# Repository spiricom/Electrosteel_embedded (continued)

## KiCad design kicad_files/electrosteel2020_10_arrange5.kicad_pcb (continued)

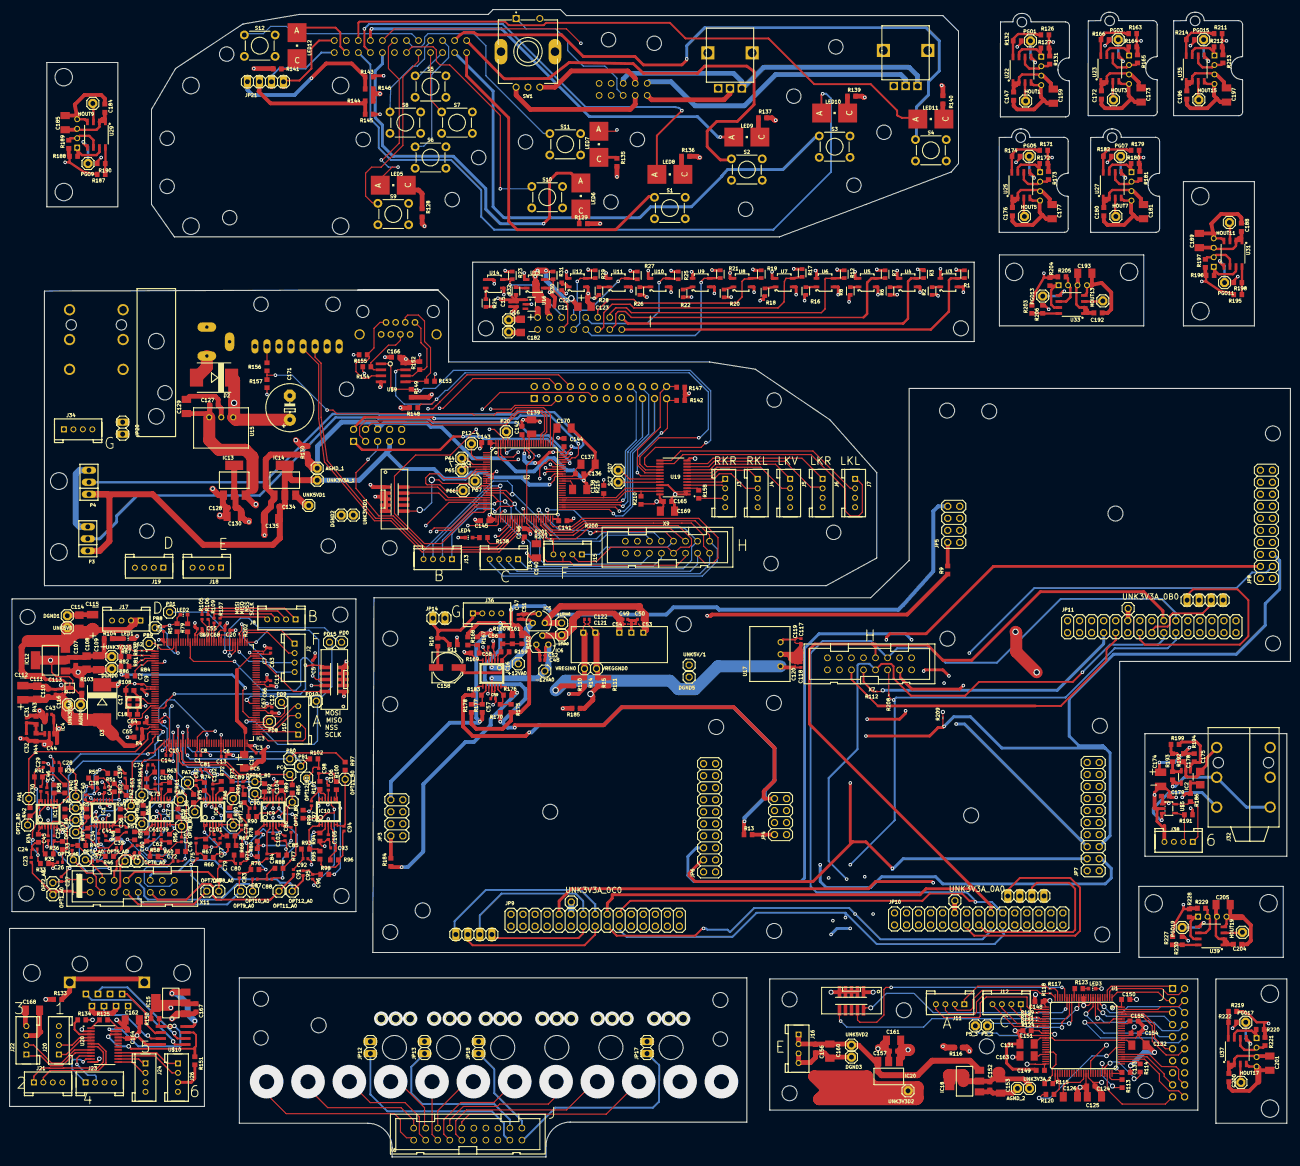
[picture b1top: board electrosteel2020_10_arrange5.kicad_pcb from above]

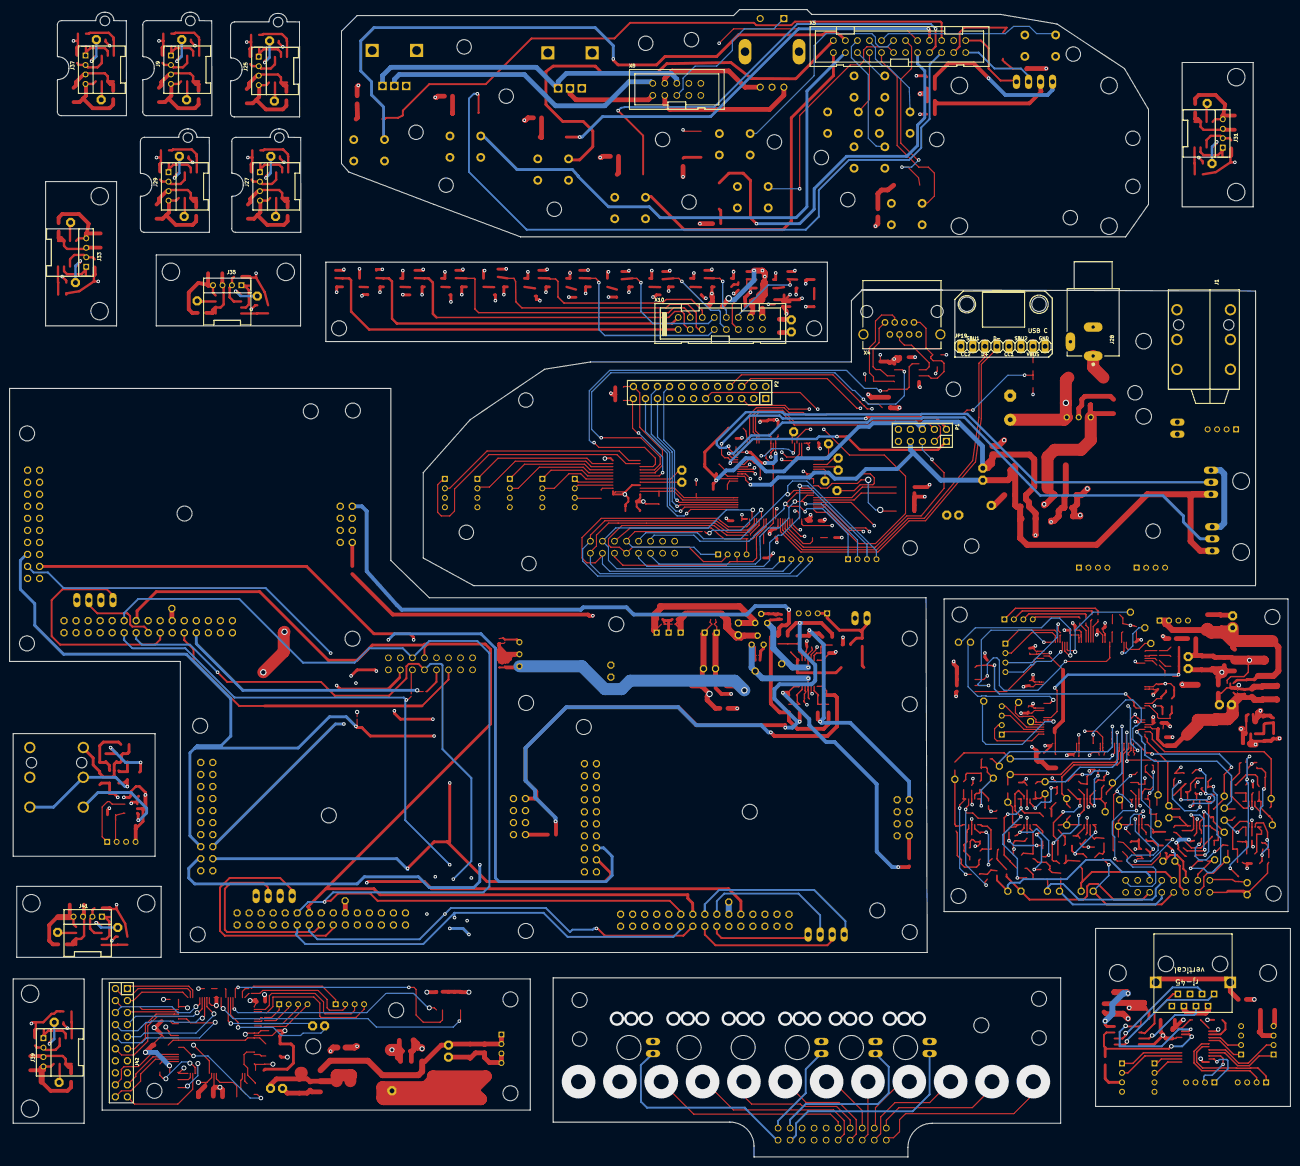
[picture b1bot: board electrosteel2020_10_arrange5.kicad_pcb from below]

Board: 4 copper layers, 270.5 x 242.3 mm, 770 parts (21 on the bottom side), 529 nets.

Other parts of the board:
R210, R215: 1.5k; R0603_16378527
SC7: 1X01
SD7: 1X01
UNK_HOLE_0: dummyfp0
UNK_HOLE_1: dummyfp1
UNK_HOLE_2: dummyfp2
UNK_HOLE_3: dummyfp3
UNK_HOLE_4: dummyfp4
UNK_HOLE_5: dummyfp5
UNK_HOLE_6: dummyfp6
UNK_HOLE_7: dummyfp7
UNK_HOLE_8: dummyfp8
UNK_HOLE_9: dummyfp9
UNK_HOLE_10: dummyfp10
UNK_HOLE_11: dummyfp11
UNK_HOLE_12: dummyfp12
UNK_HOLE_13: dummyfp13
UNK_HOLE_14: dummyfp14
UNK_HOLE_15: dummyfp15
UNK_HOLE_16: dummyfp16
UNK_HOLE_17: dummyfp17
UNK_HOLE_18: dummyfp18
UNK_HOLE_19: dummyfp19
UNK_HOLE_20: dummyfp20
UNK_HOLE_21: dummyfp21
UNK_HOLE_22: dummyfp22
UNK_HOLE_23: dummyfp23
UNK_HOLE_24: dummyfp24
UNK_HOLE_25: dummyfp25
UNK_HOLE_26: dummyfp26
UNK_HOLE_27: dummyfp27
UNK_HOLE_28: dummyfp28
UNK_HOLE_29: dummyfp29
UNK_HOLE_30: dummyfp30
UNK_HOLE_31: dummyfp31
UNK_HOLE_32: dummyfp32
UNK_HOLE_33: dummyfp33
UNK_HOLE_34: dummyfp34
UNK_HOLE_35: dummyfp35
UNK_HOLE_36: dummyfp36
UNK_HOLE_37: dummyfp37
UNK_HOLE_38: dummyfp38
UNK_HOLE_39: dummyfp39
UNK_HOLE_40: dummyfp40
UNK_HOLE_41: dummyfp41
UNK_HOLE_42: dummyfp42
UNK_HOLE_43: dummyfp43
UNK_HOLE_44: dummyfp44
UNK_HOLE_45: dummyfp45
UNK_HOLE_46: dummyfp46
UNK_HOLE_47: dummyfp47
UNK_HOLE_48: dummyfp48
UNK_HOLE_49: dummyfp49
UNK_HOLE_50: dummyfp50
UNK_HOLE_51: dummyfp51
UNK_HOLE_52: dummyfp52
UNK_HOLE_53: dummyfp53
UNK_HOLE_54: dummyfp54
UNK_HOLE_55: dummyfp55
UNK_HOLE_56: dummyfp56
UNK_HOLE_57: dummyfp57
UNK_HOLE_58: dummyfp58
UNK_HOLE_59: dummyfp59
UNK_HOLE_60: dummyfp60
UNK_HOLE_61: dummyfp61
UNK_HOLE_62: dummyfp62
UNK_HOLE_63: dummyfp63
UNK_HOLE_64: dummyfp64
UNK_HOLE_65: dummyfp65
UNK_HOLE_66: dummyfp66
UNK_HOLE_67: dummyfp67
UNK_HOLE_68: dummyfp68
UNK_HOLE_69: dummyfp69
UNK_HOLE_70: dummyfp70
UNK_HOLE_71: dummyfp71
UNK_HOLE_72: dummyfp72
UNK_HOLE_73: dummyfp73
UNK_HOLE_74: dummyfp74
UNK_HOLE_75: dummyfp75
UNK_HOLE_76: dummyfp76
UNK_HOLE_77: dummyfp77
UNK_HOLE_78: dummyfp78
UNK_HOLE_79: dummyfp79
UNK_HOLE_80: dummyfp80
UNK_HOLE_81: dummyfp81
UNK_HOLE_82: dummyfp82
UNK_HOLE_83: dummyfp83
UNK_HOLE_84: dummyfp84
UNK_HOLE_85: dummyfp85
UNK_HOLE_86: dummyfp86
UNK_HOLE_87: dummyfp87
UNK_HOLE_88: dummyfp88
UNK_HOLE_89: dummyfp89
UNK_HOLE_90: dummyfp90
UNK_HOLE_91: dummyfp91

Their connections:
3V3D5: R210.1, R215.2; also elsewhere on the board
unnamed 359: SD7.1; also elsewhere on the board
unnamed 360: SC7.1; also elsewhere on the board
SCL_B: R215.1; also elsewhere on the board
SDA_B: R210.2; also elsewhere on the board

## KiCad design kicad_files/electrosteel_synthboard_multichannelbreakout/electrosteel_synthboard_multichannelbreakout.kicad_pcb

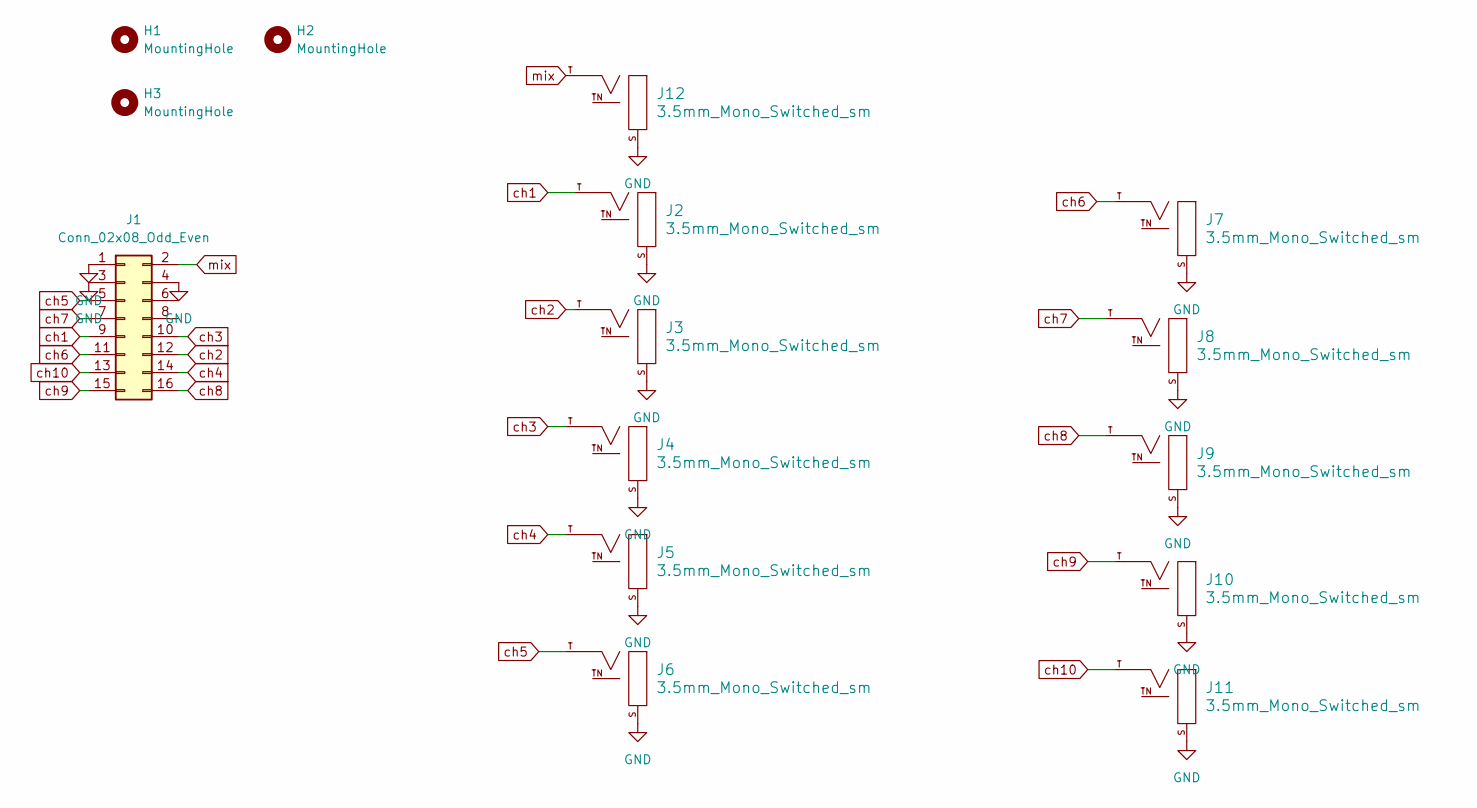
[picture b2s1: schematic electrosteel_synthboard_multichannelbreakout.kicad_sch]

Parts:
H1, H2, H3: MountingHole; MountingHole_3.2mm_M3
J1: Conn_02x08_Odd_Even; IDC-Header_2x08_P2.54mm_Vertical
J2, J3, J4, J5, J6, J7, J8, J9, J10, J11, J12: 3.5mm_Mono_Switched_sm; EighthInch_PJ398SM; Part Number WQP-WQP518MA

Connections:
GND: J1.1, J1.3, J1.4, J2.S (SHEILD), J3.S (SHEILD), J4.S (SHEILD), J5.S (SHEILD), J6.S (SHEILD), J7.S (SHEILD), J8.S (SHEILD), J9.S (SHEILD), J10.S (SHEILD), J11.S (SHEILD), J12.S (SHEILD)
ch1: J1.9, J2.T (SIG)
ch2: J1.12, J3.T (SIG)
ch3: J1.10, J4.T (SIG)
ch4: J1.14, J5.T (SIG)
ch5: J1.5, J6.T (SIG)
ch6: J1.11, J7.T (SIG)
ch7: J1.7, J8.T (SIG)
ch8: J1.16, J9.T (SIG)
ch9: J1.15, J10.T (SIG)
ch10: J1.13, J11.T (SIG)
mix: J1.2, J12.T (SIG)

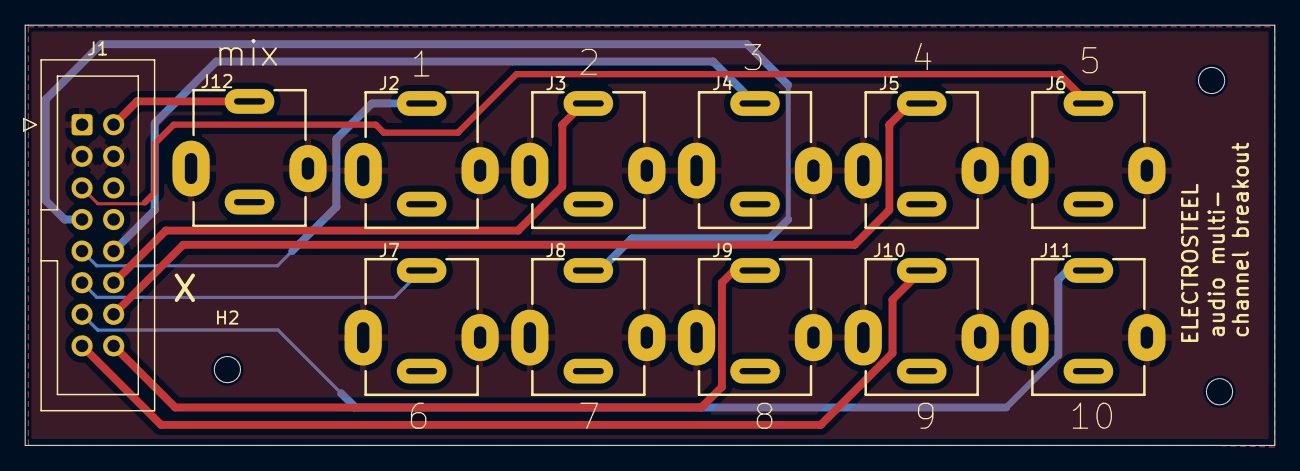
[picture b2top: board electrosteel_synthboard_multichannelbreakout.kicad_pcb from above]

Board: 2 copper layers, 100.5 x 33.8 mm, 15 parts (0 on the bottom side), 12 nets.

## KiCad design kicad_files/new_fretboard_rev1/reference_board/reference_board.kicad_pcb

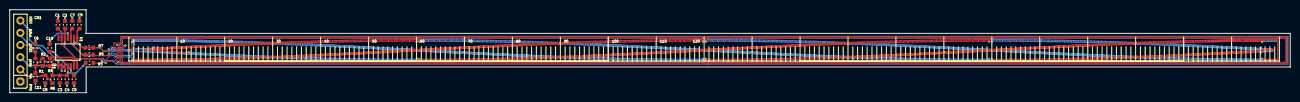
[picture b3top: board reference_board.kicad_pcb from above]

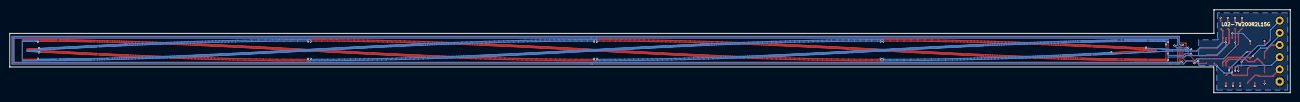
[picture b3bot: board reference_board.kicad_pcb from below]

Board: 2 copper layers, 267.1 x 17.3 mm, 25 parts (3 on the bottom side), 17 nets.

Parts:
C1, C2, C3, C4, C5, C6, C7, C8, C9, C10, C11: Capacitor NP; CAP_C_0603
CN1: Header 1x6; HDR_M_2.54_1x6
J3, J4, J5, J6, J9: JMP
R1, R2, R3, R4, R5, R6, R7: Resistor; RES_C_0603
U1: LX3302AQPW_TSSOP-14; TSSOP-14

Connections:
CL1B: J5.1, R7.2
CL2B: J6.1, R5.2
CL11: C9.2, R7.1, U1.8
CL12: C7.2, R5.1, U1.10
GND1: C1.1, C2.1, C3.1, C4.1, C5.1, C6.1, C7.1, C8.1, C9.1, C11.1, CN1.1, J5.2, J6.2, U1.2, U1.9
NetC6_2: C6.2, CN1.4, R1.1
NetC11_2: C11.2, R1.2, R2.1, U1.6
NetCN1_3: CN1.3, U1.3
NetCN1_5: CN1.5, R4.1, U1.7
NetCN1_6: CN1.6, U1.1
OSC2B: J3.2, J4.1, R3.1
OSC11: C1.2, J3.1, J9.2, U1.13
OSC12: C2.2, J4.2, U1.12
SUB: C10.1, U1.11
VDD1: C5.2, C10.2, U1.5
VIN: C8.2, CN1.2, R6.1
VIN1: C3.2, C4.2, R2.2, R3.2, R4.2, R6.2, U1.4

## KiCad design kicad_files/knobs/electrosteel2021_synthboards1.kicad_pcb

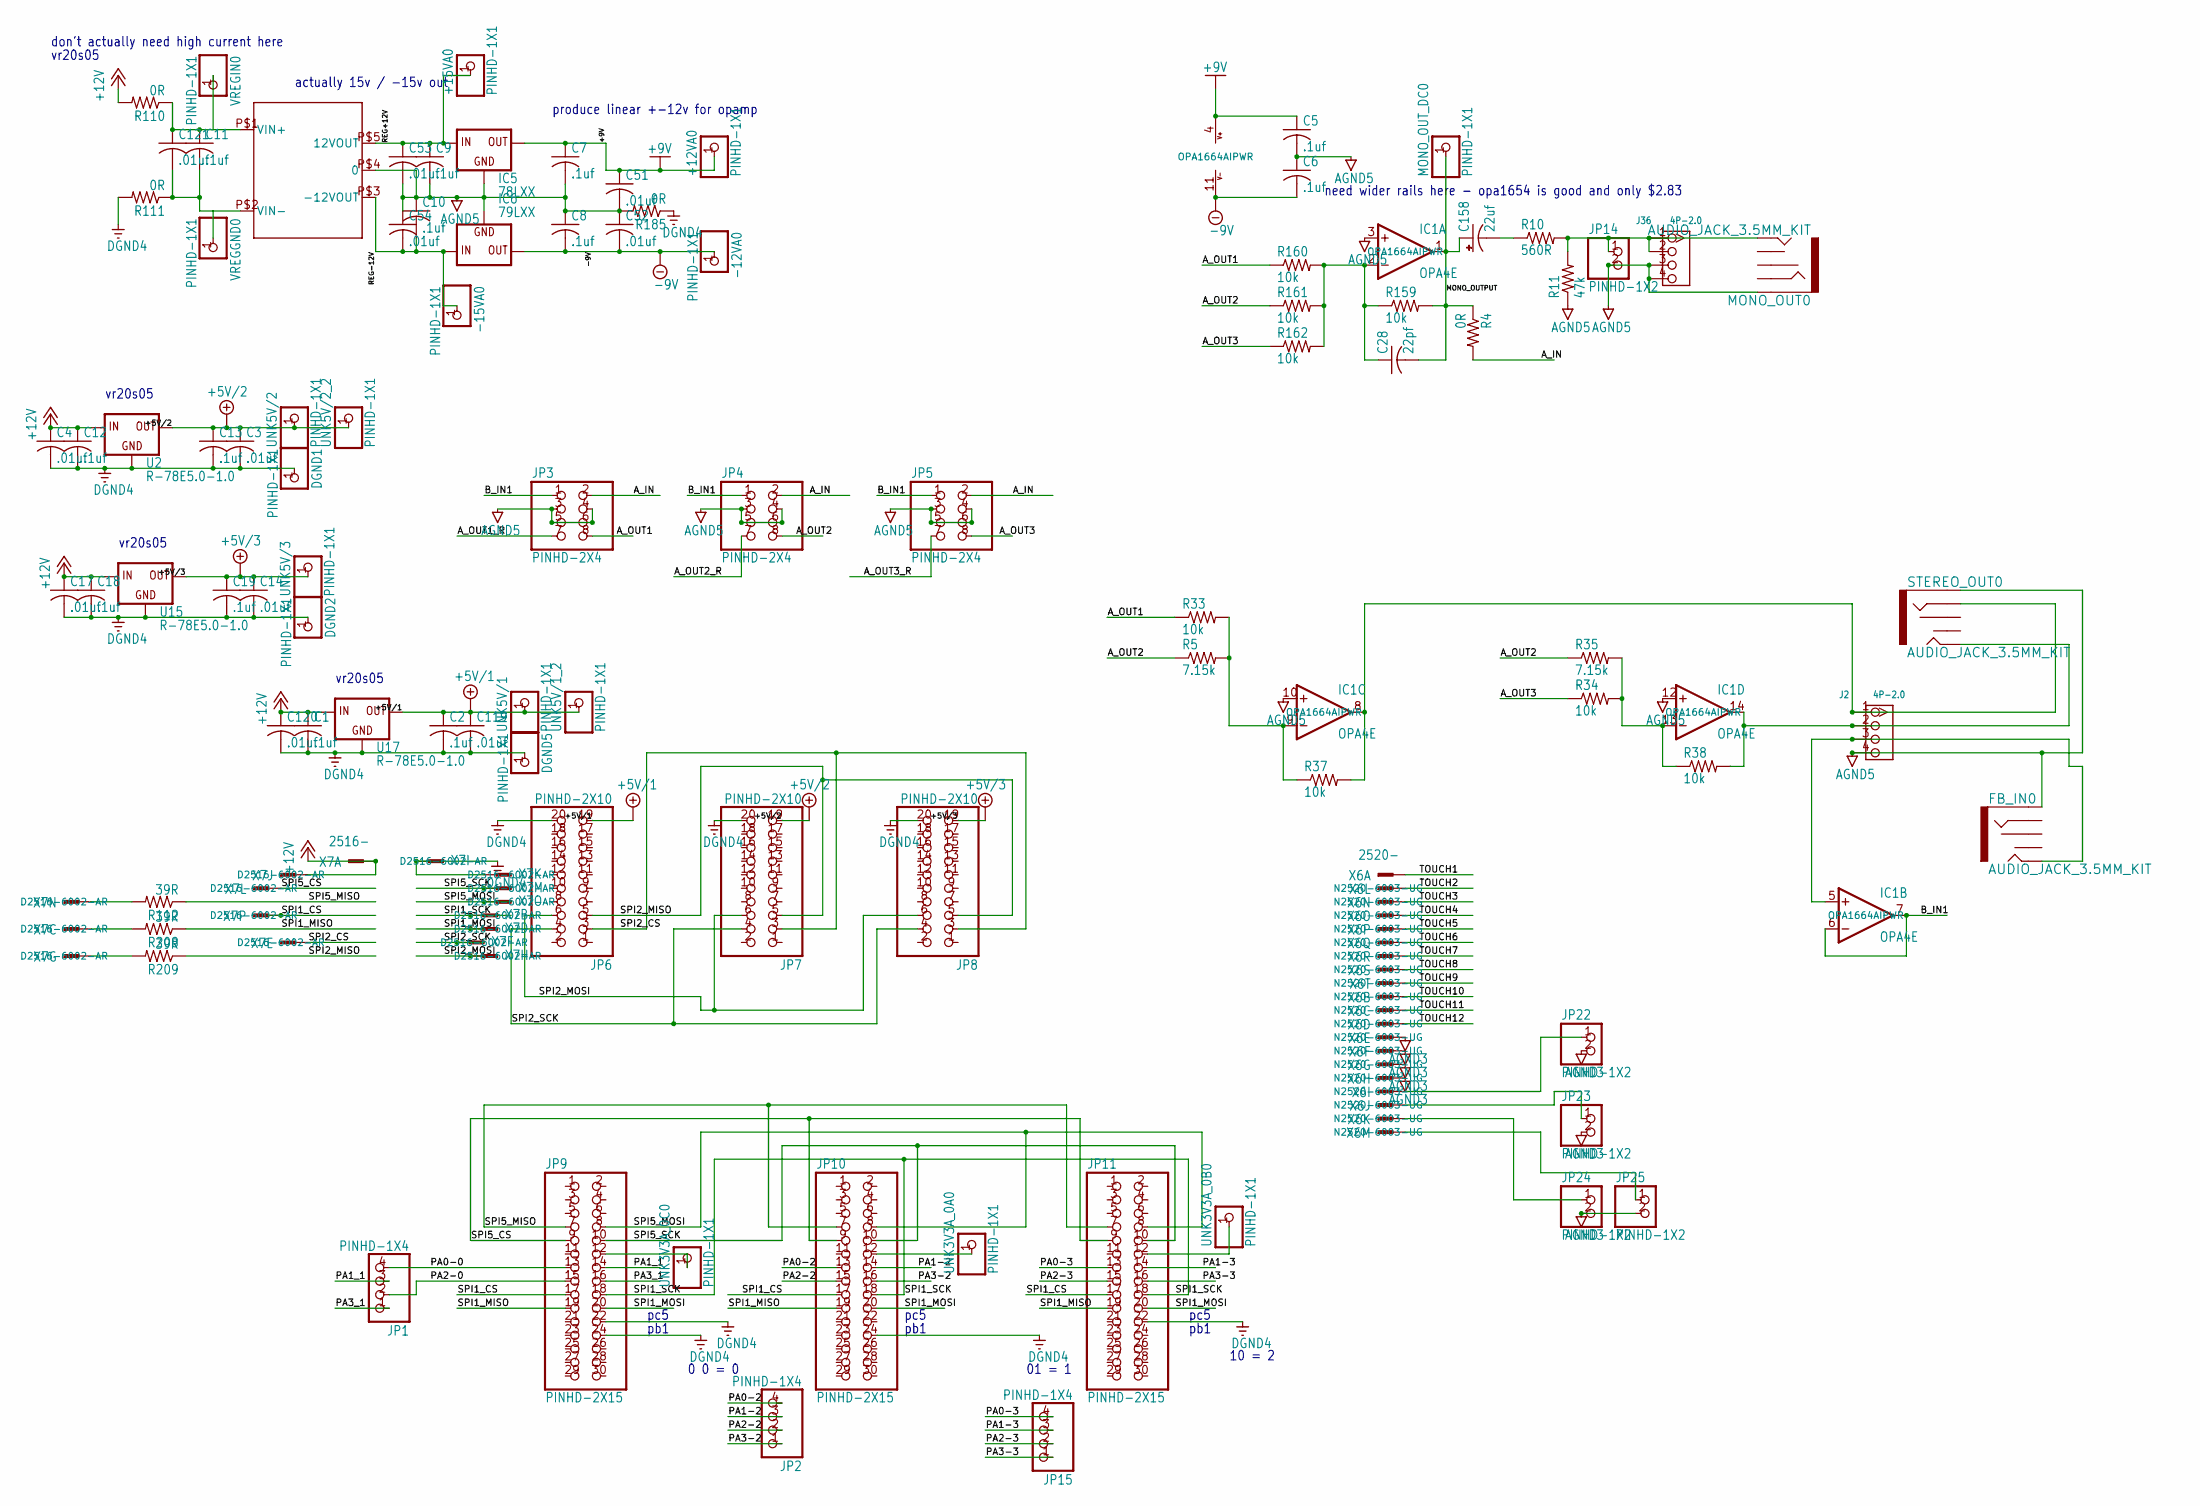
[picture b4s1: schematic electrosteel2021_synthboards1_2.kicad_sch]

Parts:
+12VA0, +15VA0: PINHD-1X1; 1X01; PARTNO *DNP
-12VA0, -15VA0: PINHD-1X1; 1X01; PARTNO *DNP
C1, C2, C5, C6, C7, C8, C9, C10, C11, C12, C13, C18, C19: .1uf; C0603; PARTNO CC0603KRX7R8BB104
C3, C4, C14, C17, C51, C52, C53, C54, C119, C120, C121: .01uf; C0603; PARTNO CC0603KRX7R8BB103
C28: 22pf; C0603; PARTNO CC0603JRNPO9BN220
C158: 22uf; PANASONIC_D; PARTNO EEE-1CA220NP
DGND1, DGND2, DGND5: PINHD-1X1; 1X01; PARTNO *DNP
FB_IN0: AUDIO_JACK_3.5MM_KIT; AUDIO-JACK-KIT; PARTNO PRT-08032
IC1: OPA4E; TSSOP14; PARTNO OPA1664AIPWR
IC5: 78LXX; PARTNO LM78L12ACZ/LFT7
IC6: 79LXX; PARTNO L79L12ACZ-TR
J2, J36: 4P-2.0; HW4-2.0; PARTNO *DNP
JP1, JP2, JP15: PINHD-1X4; 1X04; PARTNO *DNP
JP3, JP4, JP5: PINHD-2X4; 2X04; PARTNO 77313-101-08LF
JP6, JP7, JP8: PINHD-2X10; 2X10; PARTNO 77313-101-20LF
JP9, JP10, JP11: PINHD-2X15; 2X15; PARTNO 77313-101-30LF
JP14, JP22, JP23, JP24, JP25: PINHD-1X2; 1X02; PARTNO *DNP
MONO_OUT0: AUDIO_JACK_3.5MM_KIT; AUDIO-JACK-KIT; PARTNO PRT-08032
MONO_OUT_DC0: PINHD-1X1; 1X01; PARTNO *DNP
R4, R110, R111, R185: 0R; R0603; PARTNO RCS06030000Z0EA
R5, R35: 7.15k; R0603; PARTNO ERJ-3EKF7151V
R10: 560R; R0603; PARTNO ESR03EZPF5600
R11: 47k; R0603; PARTNO ESR03EZPJ473
R33, R34, R37, R38, R159, R160, R161, R162: 10k; R0603; PARTNO ESR03EZPF1002
R112, R208, R209: 39R; R0603; PARTNO RC0603JR-0739RL
STEREO_OUT0: AUDIO_JACK_3.5MM_KIT; AUDIO-JACK-KIT; PARTNO PRT-08032
U2, U15, U17: R-78E5.0-1.0; DC-DC_CONVERTER_78XX; PARTNO R-78E5.0-1.0
U$3: CMR0512S3C; PARTNO DPU01M-15
UNK3V3A_0A0, UNK3V3A_0B0, UNK3V3A_0C0, UNK5V/1, UNK5V/1_2, UNK5V/2, UNK5V/2_2, UNK5V/3: PINHD-1X1; 1X01; PARTNO *DNP
VREGGND0: PINHD-1X1; 1X01; PARTNO *DNP
VREGIN0: PINHD-1X1; 1X01; PARTNO *DNP
X6: 2520-; PAK100_2500-20; PARTNO N2520-6003-UG
X7: 2516-; PAK100_2500-16; PARTNO D2516-6002-AR

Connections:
+5V/1: C2.1, C119.1, JP6.19, U17.VOUT (OUT), UNK5V/1.1, UNK5V/1_2.1
+5V/2: C3.1, C13.1, JP7.19, U2.VOUT (OUT), UNK5V/2.1, UNK5V/2_2.1
+5V/3: C14.1, C19.1, JP8.19, U15.VOUT (OUT), UNK5V/3.1
+9V: +12VA0.1, C5.1, C7.1, C51.1, IC1.4 (V+), IC5.OUT
+12V: C1.1, C4.1, C12.1, C17.1, C18.1, C120.1, R110.2, U2.VIN (IN), U15.VIN (IN), U17.VIN (IN), X7.1, X7.3
-9V: -12VA0.1, C6.2, C8.2, C52.2, IC1.11 (V-), IC6.OUT
AGND3: JP22.2, JP23.2, JP24.2, JP25.2, X6.13, X6.14, X6.15, X6.16
AGND5: C5.2, C6.1, C7.2, C8.1, C9.2, C10.1, C51.2, C52.1, C53.2, C54.1, FB_IN0.SLEEVE, IC1.3 (+IN), IC1.10 (+IN), IC1.12 (+IN), IC5.GND, IC6.GND, J2.4, J36.3, J36.4, JP3.3, JP3.4, JP3.5, JP3.6, JP4.3, JP4.4, JP4.5, JP4.6, JP5.3, JP5.4, JP5.5, JP5.6, JP14.2, MONO_OUT0.SLEEVE, R11.1, R185.2, STEREO_OUT0.SLEEVE, U$3.P$4 (0)
A_IN: JP3.2, JP4.2, JP5.2, R4.2
A_OUT1: JP3.8, R33.1, R160.1
A_OUT1_R: JP3.7
A_OUT2: JP4.8, R5.1, R35.1, R161.1
A_OUT2_R: JP4.7
A_OUT3: JP5.8, R34.1, R162.1
A_OUT3_R: JP5.7
B_IN1: IC1.6 (-IN), IC1.7 (OUT), JP3.1, JP4.1, JP5.1
DGND4: C1.2, C2.2, C3.2, C4.2, C12.2, C13.2, C14.2, C17.2, C18.2, C19.2, C119.2, C120.2, DGND1.1, DGND2.1, DGND5.1, JP6.20, JP7.20, JP8.20, JP9.22, JP9.24, JP10.24, JP11.22, R111.2, R185.1, U2.GND, U15.GND, U17.GND, X7.2, X7.4
MONO_OUTPUT: C28.2, C158.+, IC1.1 (OUT), MONO_OUT_DC0.1, R4.1, R159.2
unnamed: IC1.9 (-IN), R5.2, R33.2, R37.1
unnamed: IC1.13 (-IN), R34.2, R35.2, R38.1
unnamed: IC1.14 (OUT), J2.2, R38.2, STEREO_OUT0.TIP
unnamed: IC1.8 (OUT), J2.1, R37.2, STEREO_OUT0.RING
unnamed: JP24.1, X6.19
unnamed: FB_IN0.TIP, IC1.5 (+IN), J2.3
unnamed: JP25.1, X6.20
unnamed: JP23.1, X6.18
unnamed: JP22.1, X6.17
unnamed: C28.1, IC1.2 (-IN), R159.1, R160.2, R161.2, R162.2
unnamed: C11.2, C121.2, R111.1, U$3.P$2 (VIN-), VREGGND0.1
unnamed: C11.1, C121.1, R110.1, U$3.P$1 (VIN+), VREGIN0.1
unnamed: C158.-, R10.1
unnamed: J36.1, J36.2, JP14.1, MONO_OUT0.TIP, R10.2, R11.2
unnamed: R209.2, X7.15
unnamed: R208.2, X7.11
unnamed: R112.2, X7.7
unnamed: JP9.12, UNK3V3A_0C0.1
unnamed: JP10.12, UNK3V3A_0A0.1
unnamed: JP11.12, UNK3V3A_0B0.1
PA0-0: JP1.4, JP9.13
PA0-2: JP2.4, JP10.13
PA0-3: JP11.13, JP15.4
PA1-2: JP2.3, JP10.14
PA1-3: JP11.14, JP15.3
PA1_1: JP1.3, JP9.14
PA2-0: JP1.2, JP9.15
PA2-2: JP2.2, JP10.15
PA2-3: JP11.15, JP15.2
PA3-2: JP2.1, JP10.16
PA3-3: JP11.16, JP15.1
PA3_1: JP1.1, JP9.16
REG+12V: +15VA0.1, C9.1, C53.1, IC5.IN, U$3.P$5 (12VOUT)
REG-12V: -15VA0.1, C10.2, C54.2, IC6.IN, U$3.P$3 (-12VOUT)
SPI1_CS: JP9.17, JP10.17, JP11.17, X7.9
SPI1_MISO: JP9.19, JP10.19, JP11.19, R208.1
SPI1_MOSI: JP9.20, JP10.20, JP11.20, X7.12
SPI1_SCK: JP9.18, JP10.18, JP11.18, X7.10
SPI2_CS: JP6.3, JP7.3, JP8.3, X7.13
SPI2_MISO: JP6.5, JP7.5, JP8.5, R209.1
SPI2_MOSI: JP6.6, JP7.6, JP8.6, X7.16
SPI2_SCK: JP6.4, JP7.4, JP8.4, X7.14
SPI5_CS: JP9.9, JP10.9, JP11.9, X7.5
SPI5_MISO: JP9.7, JP10.7, JP11.7, R112.1
SPI5_MOSI: JP9.8, JP10.8, JP11.8, X7.8
SPI5_SCK: JP9.10, JP10.10, JP11.10, X7.6
TOUCH1: X6.1
TOUCH2: X6.2
TOUCH3: X6.3
TOUCH4: X6.4
TOUCH5: X6.5
TOUCH6: X6.6
TOUCH7: X6.7
TOUCH8: X6.8
TOUCH9: X6.9
TOUCH10: X6.10
TOUCH11: X6.11
TOUCH12: X6.12

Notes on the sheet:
pb1
produce linear +-12v for opamp
pc5
vr20s05
0 0 = 0
need wider rails here - opa1654 is good and only $2.83
don't actually need high current here
actually 15v / -15v out
10 = 2
01 = 1

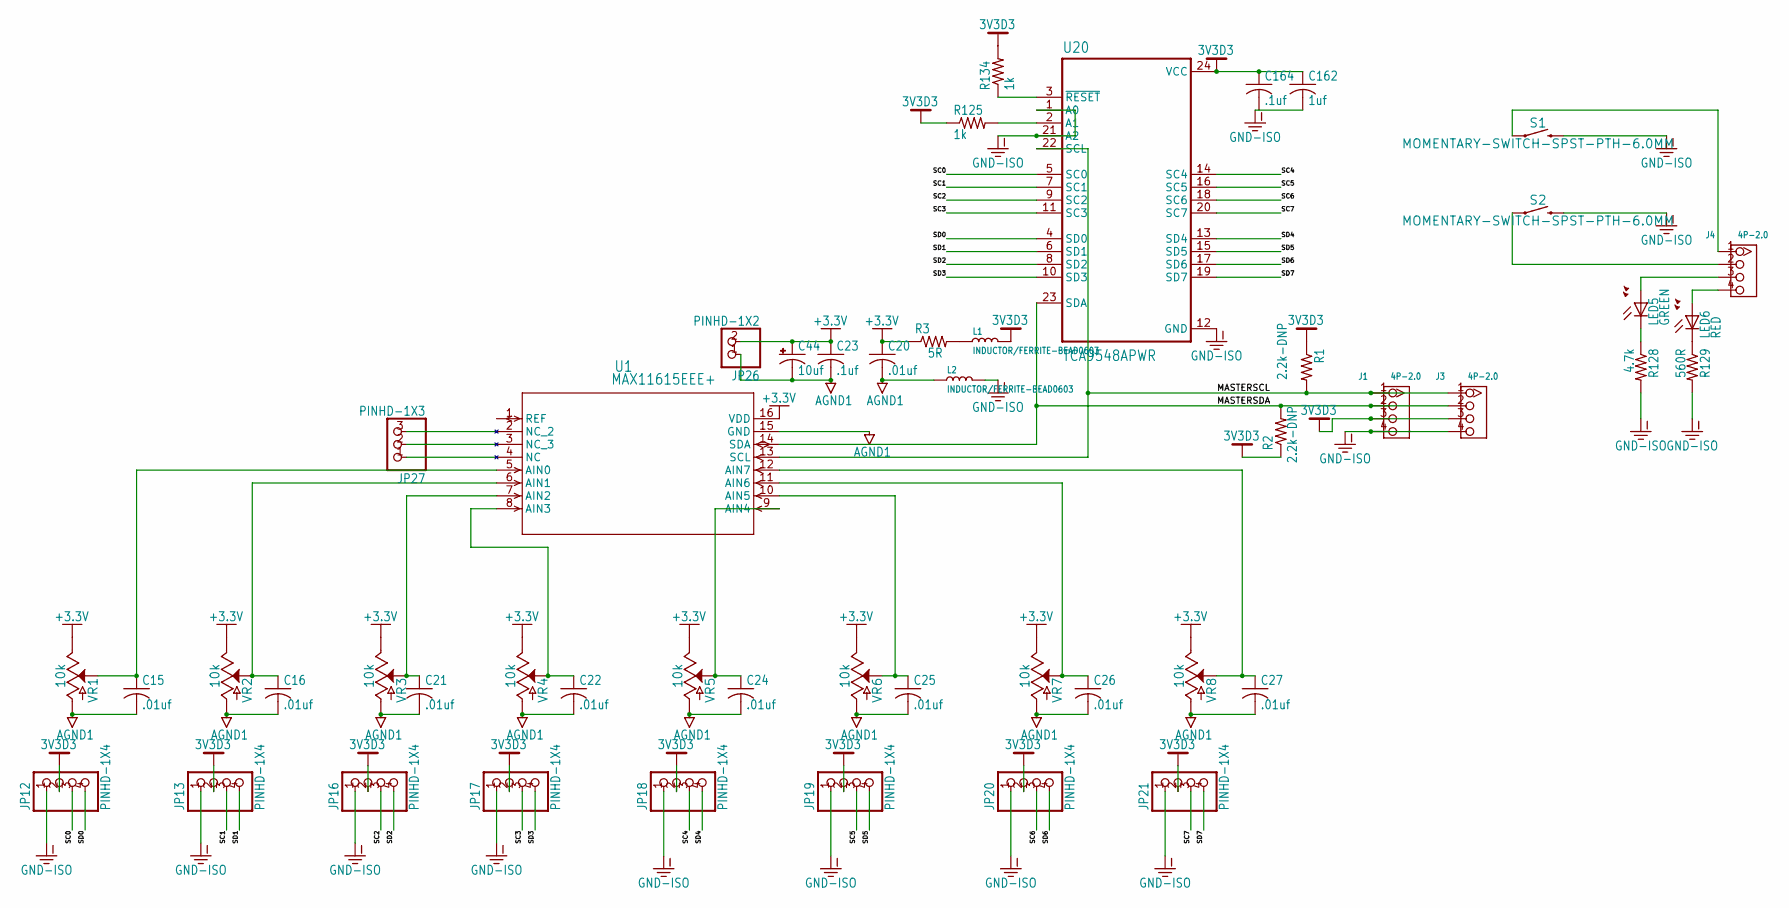
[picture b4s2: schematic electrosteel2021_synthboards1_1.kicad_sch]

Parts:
C15, C16, C20, C21, C22, C24, C25, C26, C27: .01uf; C0603; PARTNO CC0603KRX7R8BB103
C23, C164: .1uf; C0603; PARTNO CC0603KRX7R8BB104
C44: 10uf; SMC_B; PARTNO TAJB106K025RNJ
C162: 1uf; C1206K; PARTNO C3216X7R1E105K085AA
J1, J3, J4: 4P-2.0; HW4-2.0; PARTNO *DNP
JP12, JP13, JP16, JP17, JP18, JP19, JP20, JP21: PINHD-1X4; 1X04; PARTNO *DNP
JP26: PINHD-1X2; 1X02; PARTNO *DNP
JP27: PINHD-1X3; 1X03; PARTNO *DNP
L1, L2: INDUCTOR/FERRITE-BEAD0603; INDUCTOR_L0603; PARTNO FBMH1608HM470-TV
LED5: GREEN; P-LCC-2; PARTNO HSMM-A101-R00J1
LED6: RED; P-LCC-2; PARTNO HSMZ-A100-R00J1
R1, R2: 2.2k-DNP; R0603; PARTNO *DNP
R3: 5R; R0603; PARTNO RC0603JR-075R1L
R125, R134: 1k; R0603; PARTNO ESR03EZPF1001
R128: 4.7k; R0603; PARTNO CRCW06034K70FKEAHP
R129: 560R; R0603; PARTNO ESR03EZPF5600
S1, S2: MOMENTARY-SWITCH-SPST-PTH-6.0MM; TACTILE_SWITCH_PTH_6.0MM; PARTNO TL1105SPF160Q
U1: MAX11615EEE+; 21-0055H_16_MXM; PARTNO MAX11617EEE+
U20: TCA9548APWR; SOP65P640X120-24N; PARTNO TCA9548APWR
VR1, VR2, VR3, VR4, VR5, VR6, VR7, VR8: 10k; POT-PTH-ALPS; PARTNO *DNP

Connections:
3V3D3: C162.1, C164.1, J1.3, J3.3, JP12.2, JP13.2, JP16.2, JP17.2, JP18.2, JP19.2, JP20.2, JP21.2, L1.2, R1.1, R2.1, R125.1, R134.2, U20.24 (VCC)
+3.3V: C20.1, C23.1, C44.+, JP26.2, R3.1, U1.16 (VDD), VR1.P$1 (E), VR2.P$1 (E), VR3.P$1 (E), VR4.P$1 (E), VR5.P$1 (E), VR6.P$1 (E), VR7.P$1 (E), VR8.P$1 (E)
AGND1: C15.2, C16.2, C20.2, C21.2, C22.2, C23.2, C24.2, C25.2, C26.2, C27.2, C44.-, JP26.1, L2.1, U1.15 (GND), VR1.P$3 (A), VR2.P$3 (A), VR3.P$3 (A), VR4.P$3 (A), VR5.P$3 (A), VR6.P$3 (A), VR7.P$3 (A), VR8.P$3 (A)
GND-ISO: C162.2, C164.2, J1.4, J3.4, JP12.1, JP13.1, JP16.1, JP17.1, JP18.1, JP19.1, JP20.1, JP21.1, L2.2, R128.2, R129.2, S1.3 (2), S2.3 (2), U20.1 (A0), U20.12 (GND), U20.21 (A2)
MASTERSCL: J1.1, J3.1, R1.2, U1.13 (SCL), U20.22 (SCL)
MASTERSDA: J1.2, J3.2, R2.2, U1.14 (SDA), U20.23 (SDA)
unnamed: LED5.C, R128.1
unnamed: JP27.1, U1.4 (NC)
unnamed: C15.1, U1.5 (AIN0), VR1.P$2 (S)
unnamed: C16.1, U1.6 (AIN1), VR2.P$2 (S)
unnamed: C21.1, U1.7 (AIN2), VR3.P$2 (S)
unnamed: C22.1, U1.8 (AIN3), VR4.P$2 (S)
unnamed: J4.2, S2.1
unnamed: C24.1, U1.9 (AIN4), VR5.P$2 (S)
unnamed: C25.1, U1.10 (AIN5), VR6.P$2 (S)
unnamed: J4.3, LED5.A
unnamed: C26.1, U1.11 (AIN6), VR7.P$2 (S)
unnamed: C27.1, U1.12 (AIN7), VR8.P$2 (S)
unnamed: J4.4, LED6.A
unnamed: JP27.2, U1.3 (NC_3)
unnamed: R125.2, U20.2 (A1)
unnamed: JP27.3, U1.2 (NC_2)
unnamed: L1.1, R3.2
unnamed: J4.1, S1.1
unnamed: R134.1, U20.3 (~RESET)
unnamed: LED6.C, R129.1
SC0: JP12.3, U20.5 (SC0)
SC1: JP13.3, U20.7 (SC1)
SC2: JP16.3, U20.9 (SC2)
SC3: JP17.3, U20.11 (SC3)
SC4: JP18.3, U20.14 (SC4)
SC5: JP19.3, U20.16 (SC5)
SC6: JP20.3, U20.18 (SC6)
SC7: JP21.3, U20.20 (SC7)
SD0: JP12.4, U20.4 (SD0)
SD1: JP13.4, U20.6 (SD1)
SD2: JP16.4, U20.8 (SD2)
SD3: JP17.4, U20.10 (SD3)
SD4: JP18.4, U20.13 (SD4)
SD5: JP19.4, U20.15 (SD5)
SD6: JP20.4, U20.17 (SD6)
SD7: JP21.4, U20.19 (SD7)

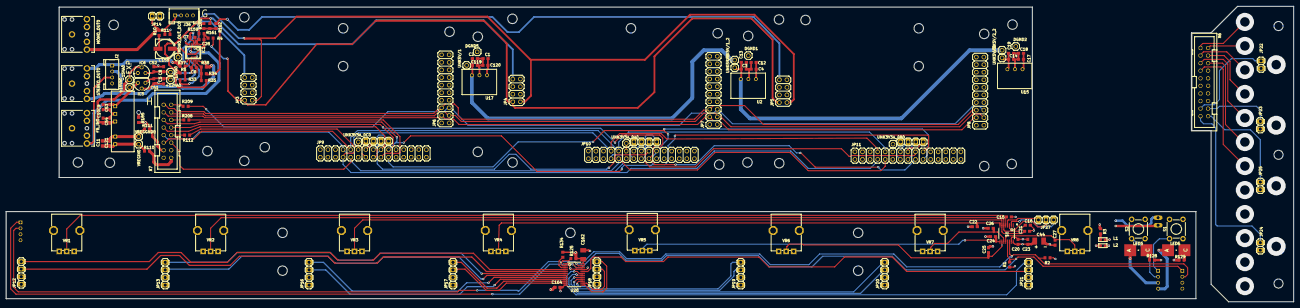
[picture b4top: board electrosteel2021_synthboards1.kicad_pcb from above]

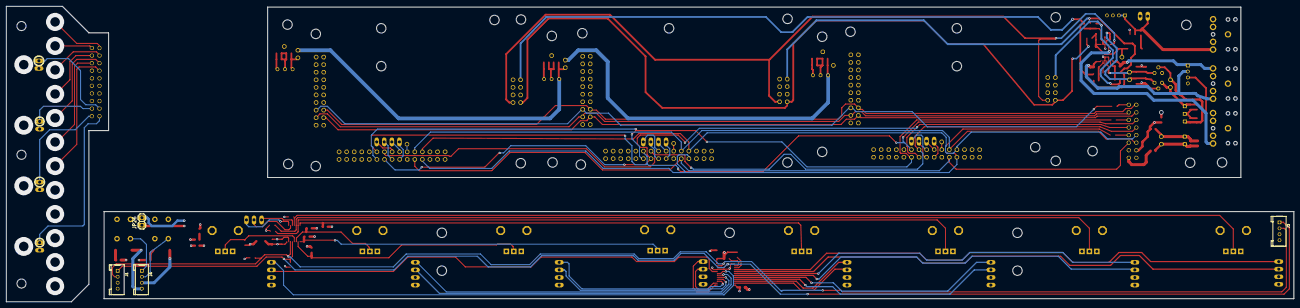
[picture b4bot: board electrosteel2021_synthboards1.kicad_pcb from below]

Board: 4 copper layers, 431.8 x 99.1 mm, 179 parts (4 on the bottom side), 103 nets.

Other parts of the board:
UNK_HOLE_0: dummyfp0
UNK_HOLE_1: dummyfp1
UNK_HOLE_2: dummyfp2
UNK_HOLE_3: dummyfp3
UNK_HOLE_4: dummyfp4
UNK_HOLE_5: dummyfp5
UNK_HOLE_6: dummyfp6
UNK_HOLE_7: dummyfp7
UNK_HOLE_8: dummyfp8
UNK_HOLE_9: dummyfp9
UNK_HOLE_10: dummyfp10
UNK_HOLE_11: dummyfp11
UNK_HOLE_12: dummyfp12
UNK_HOLE_13: dummyfp13
UNK_HOLE_14: dummyfp14
UNK_HOLE_15: dummyfp15
UNK_HOLE_16: dummyfp16
UNK_HOLE_17: dummyfp17
UNK_HOLE_18: dummyfp18
UNK_HOLE_19: dummyfp19
UNK_HOLE_20: dummyfp20
UNK_HOLE_21: dummyfp21
UNK_HOLE_22: dummyfp22
UNK_HOLE_23: dummyfp23
UNK_HOLE_24: dummyfp24
UNK_HOLE_25: dummyfp25
UNK_HOLE_26: dummyfp26
UNK_HOLE_27: dummyfp27
UNK_HOLE_28: dummyfp28
UNK_HOLE_29: dummyfp29
UNK_HOLE_30: dummyfp30
UNK_HOLE_31: dummyfp31
UNK_HOLE_32: dummyfp32
UNK_HOLE_33: dummyfp33
UNK_HOLE_34: dummyfp34
UNK_HOLE_35: dummyfp35

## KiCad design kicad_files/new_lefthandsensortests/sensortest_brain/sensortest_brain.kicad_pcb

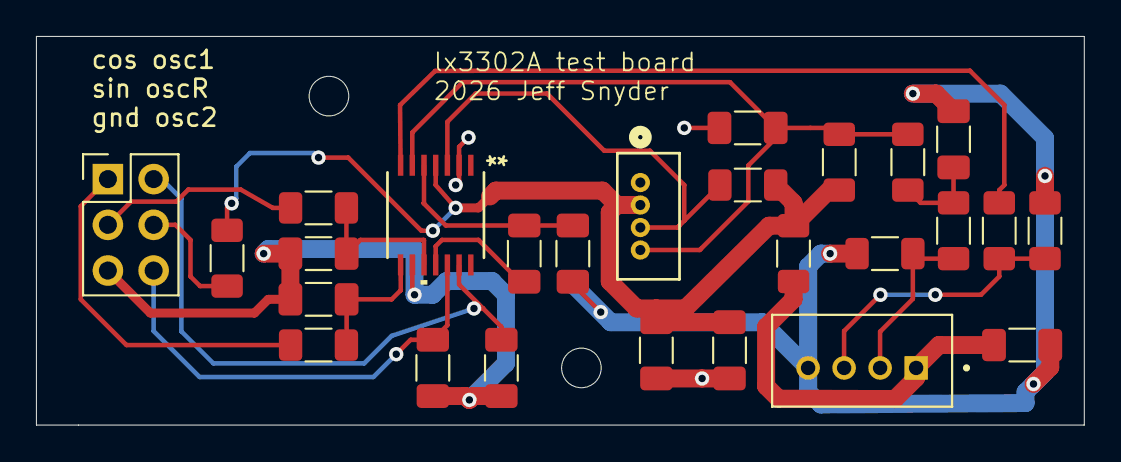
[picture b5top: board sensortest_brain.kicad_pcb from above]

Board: 2 copper layers, 58.2 x 21.6 mm, 28 parts (0 on the bottom side), 18 nets.

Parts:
C12, C13: 680pf; C_1206_3216Metric_Pad1.33x1.80mm_HandSolder
C14, C15: 10pf; C_1206_3216Metric_Pad1.33x1.80mm_HandSolder
C16: 1uf; C_1206_3216Metric_Pad1.33x1.80mm_HandSolder
C17, C20: 100nf; C_1206_3216Metric_Pad1.33x1.80mm_HandSolder
C18, C19: 6.8nf; C_1206_3216Metric_Pad1.33x1.80mm_HandSolder
C21: 1000pf; C_1206_3216Metric_Pad1.33x1.80mm_HandSolder
C22: 470nf; C_1206_3216Metric_Pad1.33x1.80mm_HandSolder
H1, H2: MountingHole; MountingHole_2.2mm_M2
J1: Conn_02x03_Counter_Clockwise; PinHeader_2x03_P2.54mm_Vertical
J10: 530470410; CONN04_530470410_MOL
J13: 110990030; SEEED_110990030
R8, R9, R10: 10R; R_1206_3216Metric_Pad1.30x1.75mm_HandSolder
R11, R103: 10k; R_1206_3216Metric_Pad1.30x1.75mm_HandSolder
R12: 221R; R_1206_3216Metric_Pad1.30x1.75mm_HandSolder
R13: 4.7R; R_1206_3216Metric_Pad1.30x1.75mm_HandSolder
R59, R94: 1k; R_1206_3216Metric_Pad1.30x1.75mm_HandSolder
R64, R93: 2k; R_1206_3216Metric_Pad1.30x1.75mm_HandSolder
U2: LX3302AQPW-TR-EASY; 14-TSSOP_MCH-L

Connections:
/CL1_A: C15.1, R10.1, U2.8 (CL1)
/CL1_B: J1.1 (+12V), R10.2
/CL2_A: C14.1, R9.1, U2.10 (CL2)
/CL2_B: J1.3 (GND), R9.2
/IO2: C19.2, J10.4, R11.1, R12.1, U2.6 (IO2)
/IO3: J10.3, R103.1, U2.3 (IO3)
/OSCreturn: J1.4 (GND), R8.2
/SUB_A: C17.1, U2.11 (SUB)
/VIN_A: C21.2, C22.2, J10.2, R8.1, R11.2, R13.1, R103.2, U2.4 (VIN)
/osc1: C13.1, J1.2 (+12V), U2.13 (OSC1)
/osc2: C12.1, J1.6 (GND), U2.12 (OSC2)
GND: C12.2, C13.2, C14.2, C15.2, C16.1, C18.1, C19.1, C20.1, C21.1, C22.1, J1.5 (GND), J10.1, J13.4, R64.2, R93.2, U2.2 (GND), U2.9 (GNDCL)
unnamed: C18.2, R12.2, R59.1
unnamed: R94.1, U2.7 (IO1)
unnamed: C16.2, C17.2, U2.5 (VDD)
PWM: J13.3, R93.1, R94.2
SENT: J13.2, R59.2, R64.1
ext_vin: C20.2, J13.1, R13.2

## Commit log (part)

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2022-12-08 adding psoc code
2022-12-08 added string pluck sensor code
2022-12-08 added EAGLE files
2022-12-08 added electrosteel audio code
2022-12-08 added new fretboard to psoc code'
2022-12-14 new string touch sensor pcb code
2022-12-30 stupid
2022-12-31 improved bar timing and testing sine wave synthesis
2022-12-31 new version of psoc code that uses current dac and lower res slider
2022-12-31 copied in electrobass synthesis, still mono though
2023-01-03 working electrosteel, doesnt take in new patches but reads electrobass patches off sdcard
2023-01-05 optimized, and now expecting new data format from brain
2023-01-05 new brain sending format, brain now takes copedents from plugin and stores them in one of 7 slots on the brain
2023-01-06 current code loads presets
2023-01-08 working electrosteel psoc code. added code to skip unconnected pedals and lever in the i2c communication. also added calibration mode to set the min and max of the levers
2023-01-08 fixed storage of copedents and calibration data so that it doesn't overlap
2023-01-09 macro knobs sensing correctly, and sped things up by commenting out midi computation of pitch bend for computer communication. Will need to put that back in once the plugin can handle it
2023-01-09 knob displays working
2023-01-09 improved the bar sensing psoc code by increasing the range of the adc, decreasing the resolution of the adc for speed reasons, and boosting the idac current slightly to fill the increased range
2023-01-17 eagle files for rev5 synthboard finished
2023-03-24 push before working
2023-04-26 started daisy version of audio boards for electrosteel
2023-04-29 got one new synthboard working, doesnt yet send firmware over i2c to other boards
2023-05-07 working on daisy port. one board works but subsequent voices still dont always wake up at startup
2023-05-11 trying daisy pc
2023-05-11 trying daisy mac
2023-05-15 working for plork session
2023-05-21 working code for electrosteel using daisy. problem was mpu settings and not waiting for qspi init before writing firmware update
2023-05-22 working daisy electrosteel, tested with all 6 boards at once. works smoothly on many presets but fails on some presets that genera version could handle. need to explore why
2023-05-22 cache invalidate seems to solve issues
2023-05-22 working very well, now need to see if SDRAM memory can run faster
2023-05-23 sdram working ok. added back additive model and got string models to both use sram instead of sdram (freeing and initing as needed).
2023-05-25 changed pluck detection stm32 to be more sensitive for electromagnetic pickup. works great!;
2023-05-28 pedal mappings working in synth presets, and fixed a pluck scaling issue
2023-07-19 added capability to stream data from computer for realtime parameter changes
2023-07-19 added gitignore
2023-07-19 added psoc version of streaming capability
2023-07-20 working on getting mapping streaming functional, its close
2023-07-20 psoc side of mapping stream sending
2023-08-04 includes bootloader
2023-08-05 changed font, added name size limits, fixed macro knob midi sending
2023-08-07 many changes with close to a working menu system, and changes to slider resolution of the bar
2023-08-08 added working transpose feature, although it doesnt yet send to the synthesis
2023-08-09 fixed volume bug on every other string, and did some cleanup;
2023-08-12 added knob freezing (untested) and corrected harmonic number calculation in stm32 code
2023-08-12 fixed octave midi send bug, and other things
2023-08-21 updating
2023-09-04 new version
2023-09-09 restructed pluck to put memory in DTCMRAM and removed last two strings to leave it at 10 strings
2023-09-10 testing with int type changes to uint_fast8_t etc. breaks things, may have to do with MPU settings and things now going over alignment breaks.
2023-09-16 changed pluck communication to 32 bytes to align to cache size and avoid alignment errors. Finished writing code to allow pluck firmware update from synth board, but then realized that the pluck IC c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
2023-09-20 little details
2023-10-17 changed priorities of spi and adc dma controllers in pluck mcu
2023-12-01 version after london
2023-12-28 added genera version for testing, and refactored files into multiple c and h, and added tTstring
2024-01-03 added string model with dispersion, tension, phantom harmonics, and rudimentary bar slide noise
2024-01-08 good working version on custom chip with new tTString ;
2024-01-10 good version of tTString and ready to test moving it to the Daisy board
2024-01-10 just changed CMSIS DSP library in daisy board
2024-01-14 vocal improved, string good
2024-01-15 working ability to store versions of nonsynth models
2024-01-15 added Cypress brain sending local preset storage data
2024-01-16 fixed ability to store locally normal synth presets
2024-01-18 preset storage stuff
2024-01-22 many small fixes and replaced CMSIS DSP oversampling with my custom one because it was messing up he gain
2024-02-05 changed volume pedal curve, fixed vocal nan, and in the middle of transferring to bootloader version
2024-02-06 shipped version 1, added internal naming of presets in sd card write, transferred to daisy board
2024-02-12 many small fixes including storing preset bug and frozen knob bug
2024-02-12 fixed many small bugs including knobFrozen bug and initialization knob settings bug
2024-02-19 improved filters, and made hardware and software more similar, added transpose ability
2024-04-15 big changes
2024-04-15 fixed copedent receive bug and added firmware version reporting
2025-04-24 current state
2025-12-27 new version, preparing for new pcb spin for 2025
2025-12-29 kicad file updated with 10 synth boards[
2026-01-04 working on sensor circuit
2026-01-04 good single channel of fretboard rev
2026-01-04 version with three coil circuits, some errors
2026-01-04 got 6 of em
2026-01-04 all circuit traces
2026-01-04 all circuit traces, fixed circuit 2
2026-01-04 all circuit traces,in position
2026-01-06 stm32 micro added
2026-01-06 mcu configured, still needs power connections and spi i2c connections
2026-01-08 finished routing - adding silkscreen
2026-01-08 silkscreen finished
2026-01-08 mostly done, adjusting silkscreen labels
2026-01-09 exported gerbers of lefthand
2026-01-10 almost done with circuits, changing sd card reader
2026-01-10 finished bom and centroid
2026-03-06 got new left hand sensor working with SENT receive on stm32 chip. still requires very wide bar and doesnt yet send to the brain microcontroller or do interpolation
2026-03-08 all 9 sensors for new left hand are working and reporting properly via SENT, working on getting transmission to other boards
2026-03-08 some kicad edits
2026-03-12 testing on genera brain for synth of pattistring
2026-03-13 worked on tPattistring implementation
2026-03-21 new test circuits for bar sensor
2026-04-08 'update'
2026-04-08 added bend range settings
2026-04-12 rhino files
2026-04-15 kicad stuff
2026-04-20 testing 96k
2026-04-22 96k version working, but physical models broken, and currently doesnt have smooth way to change samplerate with 96kdefine
2026-04-22 got 96k working
2026-04-26 in the middle of changing it
2026-04-27 changed knobs back to tExpSmooth due to too heavy a load from tDynamicSmoother
2026-05-23 updated to have 24/48 bend range, but broke note ons
2026-05-30 new brain board firmware now stores fret calibration properly but doesnt yet read it properly
